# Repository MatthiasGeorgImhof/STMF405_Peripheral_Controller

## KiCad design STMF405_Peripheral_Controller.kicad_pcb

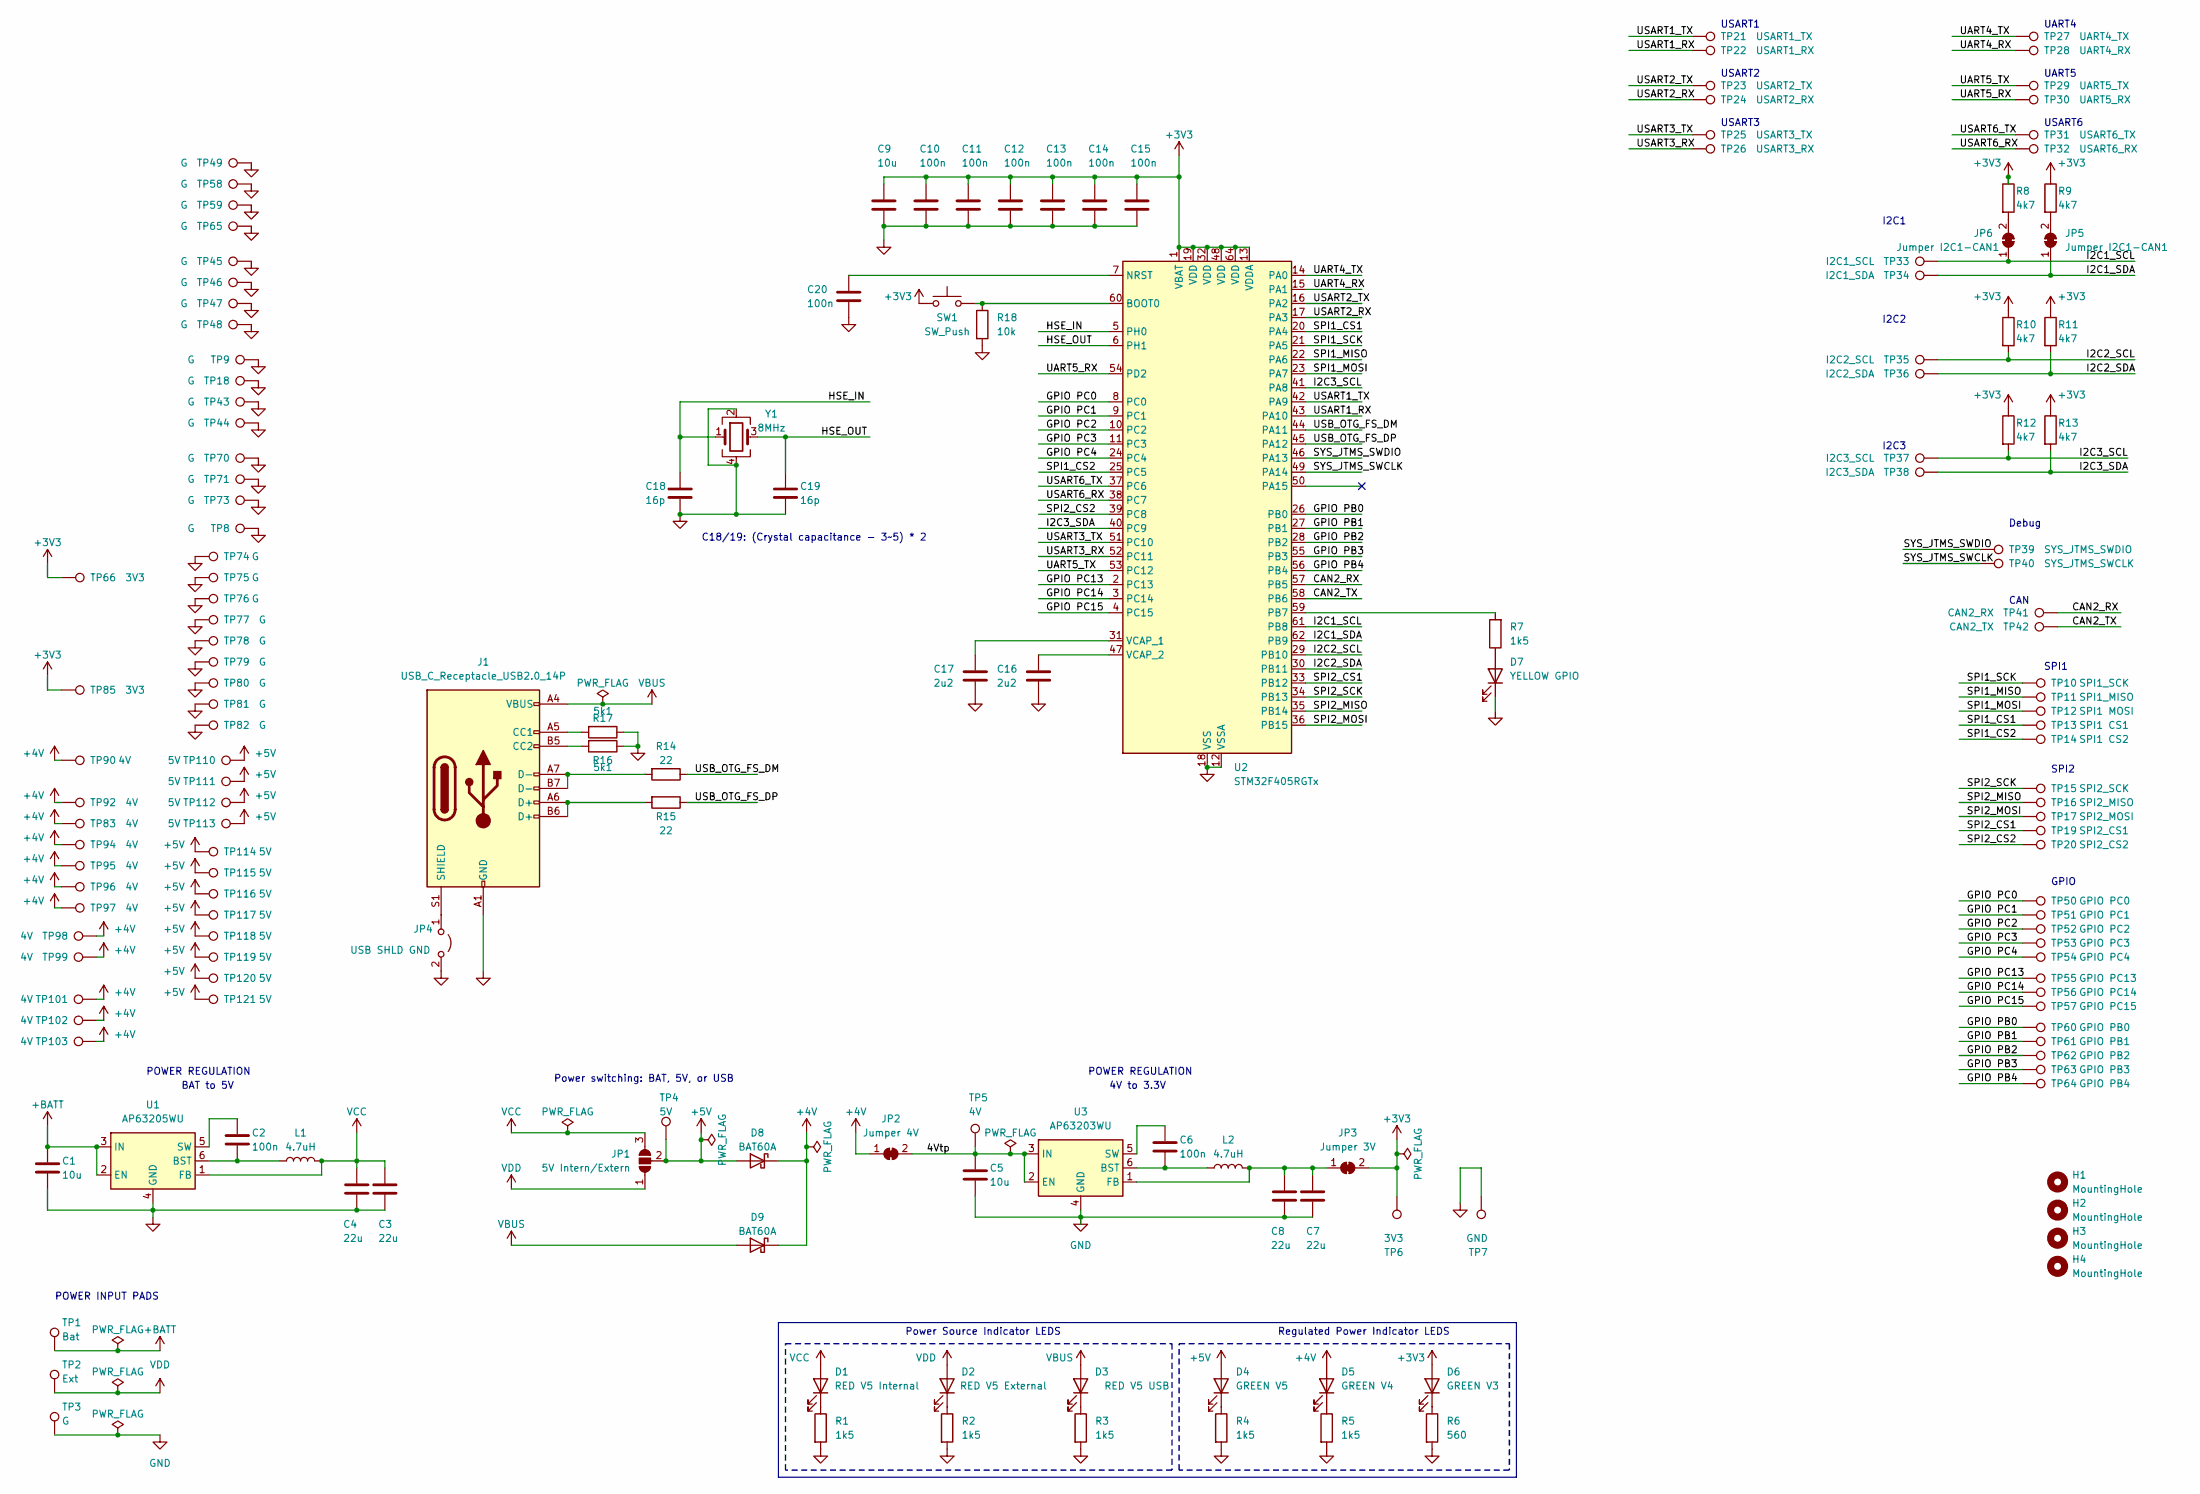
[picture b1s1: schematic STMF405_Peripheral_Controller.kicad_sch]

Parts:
C1, C5: 10u; C_0805_2012Metric; Voltage 50; Part Number GRM21BR61H106KE43L
C2, C6, C10, C11, C12, C13, C14, C15, C20: 100n; C_0402_1005Metric; Voltage 16; Part Number CC0402KRX7R7BB104
C3, C4, C7, C8: 22u; C_0805_2012Metric; Voltage 25; Part Number CL21A226MAYNNNE
C9: 10u; C_0603_1608Metric; Voltage 16; Part Number CL10X106MO8NRNC
C16, C17: 2u2; C_0402_1005Metric; Voltage 16; Part Number GRM155R61C225KE11D
C18, C19: 16p; C_0402_1005Metric; Voltage 16; Part Number CC0402JPNPO9BN160
D1: RED V5 Internal; LED_0603_1608Metric; Part Number LTST-C191KRKT
D2: RED V5 External; LED_0603_1608Metric; Part Number LTST-C191KRKT
D3: RED V5 USB; LED_0603_1608Metric; Part Number LTST-C191KRKT
D4: GREEN V5; LED_0603_1608Metric; Part Number LTST-C190GKT
D5: GREEN V4; LED_0603_1608Metric; Part Number LTST-C190GKT
D6: GREEN V3; LED_0603_1608Metric; Part Number LTST-C190GKT
D7: YELLOW GPIO; LED_0603_1608Metric; Part Number LTST-C191KFKT
D8, D9: BAT60A; D_SOD-323; Voltage 10; Part Number BAT60AE6327HTSA1
H1, H2, H3, H4: MountingHole; MountingHole_4.3mm_M4_DIN965_Pad
J1: USB_C_Receptacle_USB2.0_14P; USB_C_Receptacle_Amphenol_12401610E4-2A; Part Number 12401610E4#2A
JP1: 5V Intern/Extern; SolderJumper-3_P1.3mm_Open_Pad1.0x1.5mm
JP2: Jumper 4V; SolderJumper-2_P1.3mm_Bridged_Pad1.0x1.5mm
JP3: Jumper 3V; SolderJumper-2_P1.3mm_Bridged_Pad1.0x1.5mm
JP4: USB SHLD GND; SolderJumper-2_P1.3mm_Open_Pad1.0x1.5mm
JP5, JP6: Jumper I2C1-CAN1; SolderJumper-2_P1.3mm_Bridged_Pad1.0x1.5mm
L1, L2: 4.7uH; L_0603_1608Metric; Part Number SDFL1608Q4R7KTF
R1, R2, R3, R4, R5, R7: 1k5; R_0402_1005Metric; Part Number RC0402FR-071K5L
R6: 560; R_0402_1005Metric; Part Number RC0402FR-07560RL
R8, R9, R10, R11, R12, R13: 4k7; R_0402_1005Metric; Part Number RC0402FR-074K7L
R14, R15: 22; R_0402_1005Metric; Part Number RC0402FR-0722RL
R16, R17: 5k1; R_0402_1005Metric; Part Number RC0402FR-075K1L
R18: 10k; R_0402_1005Metric; Part Number RC0402FR-0710KL
SW1: SW_Push; SW_SPST_EVQPE1; Part Number EVQPE104K
TP1: Bat; TestPoint_Pad_2.0x2.0mm
TP2: Ext; TestPoint_Pad_2.0x2.0mm
TP3: G; TestPoint_Pad_2.0x2.0mm
TP4: 5V; TestPoint_Pad_2.0x2.0mm
TP5: 4V; TestPoint_Pad_2.0x2.0mm
TP6: 3V3; TestPoint_Pad_2.0x2.0mm
TP7: GND; TestPoint_Pad_2.0x2.0mm
TP8, TP9, TP18, TP43, TP44, TP45, TP46, TP47, TP48, TP49, TP58, TP59, TP65, TP70, TP71, TP73, TP74, TP75, TP76, TP77, TP78, TP79, TP80, TP81, TP82: G; TestPoint_Pad_1.0x1.5mm
TP10: SPI1_SCK; TestPoint_Pad_1.0x1.5mm
TP11: SPI1_MISO; TestPoint_Pad_1.0x1.5mm
TP12: SPI1 MOSI; TestPoint_Pad_1.0x1.5mm
TP13: SPI1 CS1; TestPoint_Pad_1.0x1.5mm
TP14: SPI1 CS2; TestPoint_Pad_1.0x1.5mm
TP15: SPI2_SCK; TestPoint_Pad_1.0x1.5mm
TP16: SPI2_MISO; TestPoint_Pad_1.0x1.5mm
TP17: SPI2_MOSI; TestPoint_Pad_1.0x1.5mm
TP19: SPI2_CS1; TestPoint_Pad_1.0x1.5mm
TP20: SPI2_CS2; TestPoint_Pad_1.0x1.5mm
TP21: USART1_TX; TestPoint_Pad_1.0x1.5mm
TP22: USART1_RX; TestPoint_Pad_1.0x1.5mm
TP23: USART2_TX; TestPoint_Pad_1.0x1.5mm
TP24: USART2_RX; TestPoint_Pad_1.0x1.5mm
TP25: USART3_TX; TestPoint_Pad_1.0x1.5mm
TP26: USART3_RX; TestPoint_Pad_1.0x1.5mm
TP27: UART4_TX; TestPoint_Pad_1.0x1.5mm
TP28: UART4_RX; TestPoint_Pad_1.0x1.5mm
TP29: UART5_TX; TestPoint_Pad_1.0x1.5mm
TP30: UART5_RX; TestPoint_Pad_1.0x1.5mm
TP31: USART6_TX; TestPoint_Pad_1.0x1.5mm
TP32: USART6_RX; TestPoint_Pad_1.0x1.5mm
TP33: I2C1_SCL; TestPoint_Pad_1.0x1.5mm
TP34: I2C1_SDA; TestPoint_Pad_1.0x1.5mm
TP35: I2C2_SCL; TestPoint_Pad_1.0x1.5mm
TP36: I2C2_SDA; TestPoint_Pad_1.0x1.5mm
TP37: I2C3_SCL; TestPoint_Pad_1.0x1.5mm
TP38: I2C3_SDA; TestPoint_Pad_1.0x1.5mm
TP39: SYS_JTMS_SWDIO; TestPoint_Pad_1.0x1.5mm
TP40: SYS_JTMS_SWCLK; TestPoint_Pad_1.0x1.5mm
TP41: CAN2_RX; TestPoint_Pad_1.0x1.5mm
TP42: CAN2_TX; TestPoint_Pad_1.0x1.5mm
TP50: GPIO PC0; TestPoint_Pad_1.0x1.5mm
TP51: GPIO PC1; TestPoint_Pad_1.0x1.5mm
TP52: GPIO PC2; TestPoint_Pad_1.0x1.5mm
TP53: GPIO PC3; TestPoint_Pad_1.0x1.5mm
TP54: GPIO PC4; TestPoint_Pad_1.0x1.5mm
TP55: GPIO PC13; TestPoint_Pad_1.0x1.5mm
TP56: GPIO PC14; TestPoint_Pad_1.0x1.5mm
TP57: GPIO PC15; TestPoint_Pad_1.0x1.5mm
TP60: GPIO PB0; TestPoint_Pad_1.0x1.5mm
TP61: GPIO PB1; TestPoint_Pad_1.0x1.5mm
TP62: GPIO PB2; TestPoint_Pad_1.0x1.5mm
TP63: GPIO PB3; TestPoint_Pad_1.0x1.5mm
TP64: GPIO PB4; TestPoint_Pad_1.0x1.5mm
TP66, TP85: 3V3; TestPoint_Pad_1.0x1.5mm
TP83, TP90, TP92, TP94, TP95, TP96, TP97, TP98, TP99, TP101, TP102, TP103: 4V; TestPoint_Pad_1.0x1.5mm
TP110, TP111, TP112, TP113, TP114, TP115, TP116, TP117, TP118, TP119, TP120, TP121: 5V; TestPoint_Pad_1.0x1.5mm
U1: AP63205WU; TSOT-23-6; Part Number AP63205WU-7
U2: STM32F405RGTx; LQFP-64_10x10mm_P0.5mm; Part Number STM32F405RGT6
U3: AP63203WU; TSOT-23-6; Part Number AP63203WU-7
Y1: 8MHz; Crystal_SMD_3225-4Pin_3.2x2.5mm; Part Number ECS-80-12-33-JGN-TR

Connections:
+3V3: C9.1, C10.1, C11.1, C12.1, C13.1, C14.1, C15.1, D6.2 (A), JP3.2 (B), R8.1, R9.1, R10.1, R11.1, R12.1, R13.1, SW1.2, TP6.1, TP66.1, TP85.1, U2.1 (VBAT), U2.13 (VDDA), U2.19 (VDD), U2.32 (VDD), U2.48 (VDD), U2.64 (VDD)
+4V: D5.2 (A), D8.1 (K), D9.1 (K), JP2.1 (A), TP83.1, TP90.1, TP92.1, TP94.1, TP95.1, TP96.1, TP97.1, TP98.1, TP99.1, TP101.1, TP102.1, TP103.1
+5V: D4.2 (A), D8.2 (A), JP1.2 (C), TP4.1, TP110.1, TP111.1, TP112.1, TP113.1, TP114.1, TP115.1, TP116.1, TP117.1, TP118.1, TP119.1, TP120.1, TP121.1
+BATT: C1.1, TP1.1, U1.2 (EN), U1.3 (IN)
/4Vtp: C5.1, JP2.2 (B), TP5.1, U3.2 (EN), U3.3 (IN)
/CAN2_RX: TP41.1, U2.57 (PB5)
/CAN2_TX: TP42.1, U2.58 (PB6)
/GPIO PB0: TP60.1, U2.26 (PB0)
/GPIO PB1: TP61.1, U2.27 (PB1)
/GPIO PB2: TP62.1, U2.28 (PB2)
/GPIO PB3: TP63.1, U2.55 (PB3)
/GPIO PB4: TP64.1, U2.56 (PB4)
/GPIO PC0: TP50.1, U2.8 (PC0)
/GPIO PC1: TP51.1, U2.9 (PC1)
/GPIO PC2: TP52.1, U2.10 (PC2)
/GPIO PC3: TP53.1, U2.11 (PC3)
/GPIO PC4: TP54.1, U2.24 (PC4)
/GPIO PC13: TP55.1, U2.2 (PC13)
/GPIO PC14: TP56.1, U2.3 (PC14)
/GPIO PC15: TP57.1, U2.4 (PC15)
/HSE_IN: C18.1, U2.5 (PH0), Y1.1
/HSE_OUT: C19.1, U2.6 (PH1), Y1.3
/I2C1_SCL: JP6.1 (A), TP33.1, U2.61 (PB8)
/I2C1_SDA: JP5.1 (A), TP34.1, U2.62 (PB9)
/I2C2_SCL: R10.2, TP35.1, U2.29 (PB10)
/I2C2_SDA: R11.2, TP36.1, U2.30 (PB11)
/I2C3_SCL: R12.2, TP37.1, U2.41 (PA8)
/I2C3_SDA: R13.2, TP38.1, U2.40 (PC9)
/SPI1_CS1: TP13.1, U2.20 (PA4)
/SPI1_CS2: TP14.1, U2.25 (PC5)
/SPI1_MISO: TP11.1, U2.22 (PA6)
/SPI1_MOSI: TP12.1, U2.23 (PA7)
/SPI1_SCK: TP10.1, U2.21 (PA5)
/SPI2_CS1: TP19.1, U2.33 (PB12)
/SPI2_CS2: TP20.1, U2.39 (PC8)
/SPI2_MISO: TP16.1, U2.35 (PB14)
/SPI2_MOSI: TP17.1, U2.36 (PB15)
/SPI2_SCK: TP15.1, U2.34 (PB13)
/SYS_JTMS_SWCLK: TP40.1, U2.49 (PA14)
/SYS_JTMS_SWDIO: TP39.1, U2.46 (PA13)
/UART4_RX: TP28.1, U2.15 (PA1)
/UART4_TX: TP27.1, U2.14 (PA0)
/UART5_RX: TP30.1, U2.54 (PD2)
/UART5_TX: TP29.1, U2.53 (PC12)
/USART1_RX: TP22.1, U2.43 (PA10)
/USART1_TX: TP21.1, U2.42 (PA9)
/USART2_RX: TP24.1, U2.17 (PA3)
/USART2_TX: TP23.1, U2.16 (PA2)
/USART3_RX: TP26.1, U2.52 (PC11)
/USART3_TX: TP25.1, U2.51 (PC10)
/USART6_RX: TP32.1, U2.38 (PC7)
/USART6_TX: TP31.1, U2.37 (PC6)
/USB_OTG_FS_DM: R14.1, U2.44 (PA11)
/USB_OTG_FS_DP: R15.1, U2.45 (PA12)
GND: C1.2, C3.2, C4.2, C5.2, C7.2, C8.2, C9.2, C10.2, C11.2, C12.2, C13.2, C14.2, C15.2, C16.2, C17.2, C18.2, C19.2, C20.2, D7.1 (K), J1.A1 (GND), J1.A12 (GND), J1.B1 (GND), J1.B12 (GND), JP4.2 (B), R1.2, R2.2, R3.2, R4.2, R5.2, R6.2, R16.1, R17.1, R18.2, TP3.1, TP7.1, TP8.1, TP9.1, TP18.1, TP43.1, TP44.1, TP45.1, TP46.1, TP47.1, TP48.1, TP49.1, TP58.1, TP59.1, TP65.1, TP70.1, TP71.1, TP73.1, TP74.1, TP75.1, TP76.1, TP77.1, TP78.1, TP79.1, TP80.1, TP81.1, TP82.1, U1.4 (GND), U2.12 (VSSA), U2.18 (VSS), U2.63 (VSS), U3.4 (GND), Y1.2, Y1.4
unnamed: D1.1 (K), R1.1
unnamed: D2.1 (K), R2.1
unnamed: D3.1 (K), R3.1
unnamed: D4.1 (K), R4.1
unnamed: D5.1 (K), R5.1
unnamed: D6.1 (K), R6.1
unnamed: D7.2 (A), R7.1
unnamed: J1.A5 (CC1), R17.2
unnamed: J1.B5 (CC2), R16.2
unnamed: J1.A6 (D+), J1.B6 (D+), R15.2
unnamed: J1.A7 (D-), J1.B7 (D-), R14.2
unnamed: J1.S1 (SHIELD), JP4.1 (A)
unnamed: C7.1, C8.1, JP3.1 (A), L2.2, U3.1 (FB)
unnamed: JP5.2 (B), R9.2
unnamed: JP6.2 (B), R8.2
unnamed: C2.2, L1.1, U1.6 (BST)
unnamed: C2.1, U1.5 (SW)
unnamed: R18.1, SW1.1, U2.60 (BOOT0)
unnamed: C20.1, U2.7 (NRST)
unnamed: R7.2, U2.59 (PB7)
unnamed: C17.1, U2.31 (VCAP_1)
unnamed: C16.1, U2.47 (VCAP_2)
unnamed: C6.2, L2.1, U3.6 (BST)
unnamed: C6.1, U3.5 (SW)
VBUS: D3.2 (A), D9.2 (A), J1.A4 (VBUS), J1.A9 (VBUS), J1.B4 (VBUS), J1.B9 (VBUS)
VCC: C3.1, C4.1, D1.2 (A), JP1.3 (B), L1.2, U1.1 (FB)
VDD: D2.2 (A), JP1.1 (A), TP2.1

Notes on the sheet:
UART4
GPIO
4V to 3.3V
Debug
Power switching: BAT, 5V, or USB
Power Source Indicator LEDS
CAN
POWER REGULATION
I2C1
BAT to 5V
UART5
I2C3
USART2
SPI2
SPI1
USART3
POWER INPUT PADS
I2C2
USART6
C18/19: (Crystal capacitance - 3~5) * 2
USART1
Regulated Power Indicator LEDS

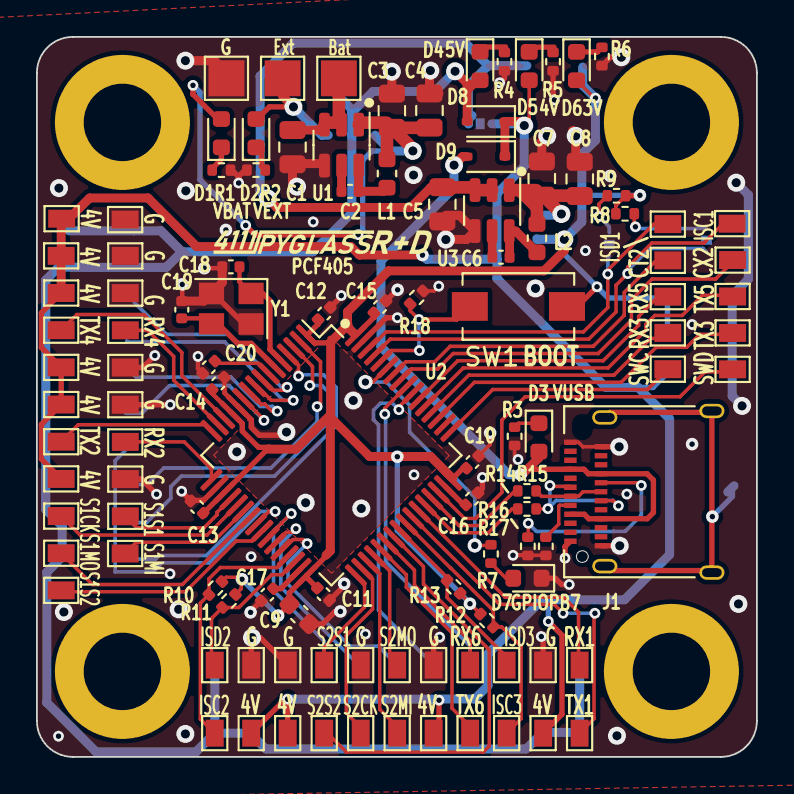
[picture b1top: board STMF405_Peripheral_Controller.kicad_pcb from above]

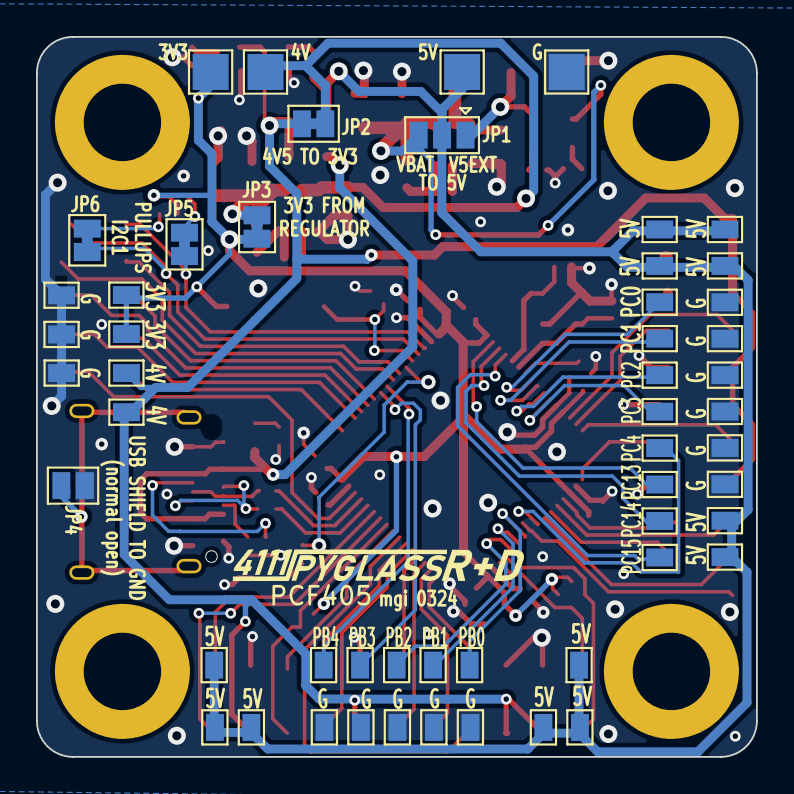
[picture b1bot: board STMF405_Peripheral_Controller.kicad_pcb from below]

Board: 2 copper layers, 40.0 x 40.0 mm, 168 parts (53 on the bottom side), 82 nets.

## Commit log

2024-07-22 initialize repo
2024-07-22 push project
